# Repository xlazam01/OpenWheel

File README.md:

# OpenWheel

<p align="center"></p>

Open-source motorised filter wheel for astrophotography (up to 9 filters; the DIY release takes
4 × 2"). It appears on the PC as a USB serial device, is detected automatically, and is driven from
NINA and other ASCOM clients, or from KStars/Ekos through INDI.

## Documentation

| | |
|---|---|
| [Build guide](docs/BUILD.md) | step-by-step pages drawn from the CAD model, also as [PDF](docs/build/OpenWheel-build-guide.pdf) |
| [Bill of materials](docs/BOM.md) | printed, CNC and bought parts with sources; PCB parts with LCSC numbers ([CSV](docs/bom/)) |
| [User manual](docs/MANUAL.md) | mounting, drivers, buttons and LEDs, errors, changing filters, firmware update |
| [DIY notes](docs/DIY_NOTES.md) | every dimension and design decision behind the mechanics |
| [Schematic](docs/hw/OpenWheel-schematic.pdf) | PCB schematic (PDF); board renders: [top](docs/hw/pcb_top.png), [bottom](docs/hw/pcb_bottom.png), [3D](docs/hw/pcb_iso.png) |
| [Protocol](docs/PROTOCOL.md) | serial commands for your own software |

| | |
|---|---|
| MCU | STM32G0B1 (native USB CDC), PlatformIO + Arduino framework |
| Motor | stepper on a TMC2209 (UART configured) |
| Position | hall sensor + a different-length magnet per slot; calibration, filter names and focus offsets are stored in a 24AA64 I2C EEPROM |
| Host protocol | text commands `:NN[params]#`, 115200 baud, every command is answered |
| USB ID | VID `0x1209` ([pid.codes](https://pid.codes)), PID see [docs/USB_IDS.md](docs/USB_IDS.md) |

<p align="center">

</p>
<p align="center"><sub>Controller PCB (V3.2, rendered from <code>hw/filter_wheel.kicad_pcb</code>)</sub></p>

## Repository layout

| Folder | Content |
|---|---|
| `fw/` | firmware (PlatformIO project, target `STM32G0B1`) |
| `hw/` | KiCad schematic and PCB |
| `cad/diy/` | mechanical models of the DIY release (SolidCraft sources, STEP, 3MF for printing) |
| `driver/ASCOM/` | ASCOM driver for NINA & co.: core library, COM local server, setup dialog, tests, installer script |
| `driver/INDI/` | INDI driver for KStars/Ekos on Linux, wheel simulator, tests |
| `tools/gui/` | small Python/Qt test GUI |
| `tools/hwtest/` | pytest acceptance tests that run against a real board over USB |
| `tools/manual/` | generator for the build-guide pages (CAD view DXF → SVG/PDF) |
| `docs/` | build guide, BOM, user manual, DIY notes, protocol reference, USB IDs |
| `release/` | one folder per release: firmware binary, PCB fabrication files, CAD exports — latest [1.1.0](release/1.1.0/README.md) |

## Build and flash

```text
pio run -d fw -e STM32G0B1                 # build
pio run -d fw -e STM32G0B1 -t upload       # flash over USB (DFU)
```

**Entering the bootloader (DFU):**

- **Hold the CCW button while powering on.** The CCW button is wired to the **BOOT0** pin, so the
  STM32 starts its built-in USB DFU bootloader instead of the firmware.
- On a running wheel the command `:31#` does the same without touching the button (flag in RAM + reset, see
  [docs/BOOTLOADER.md](docs/BOOTLOADER.md)).

Open `fw/` (not the repository root) in VS Code with the PlatformIO extension.

## Using the wheel

- **Buttons:** single click on CW / CCW moves to the next / previous slot, double click homes,
  a long press on CW starts calibration. Holding **CW** while powering on also starts calibration;
  holding **CCW** while powering on enters DFU (see above).
- **LEDs:** status LED 1 blinks while moving; LED 2 blinks the slot number on arrival; both LEDs
  alternate on an error (read the cause with `:33#` / `:34#`).
- **Test GUI:** `pip install -r tools/gui/requirements.txt && python tools/gui/main.py`
- **Hardware tests:** `python -m pytest tools/hwtest --port COM13`

## Serial protocol

Full reference with every command: [docs/PROTOCOL.md](docs/PROTOCOL.md). In short:

- **Link:** USB CDC serial port (115200 8N1, the speed is nominal over USB). Do not rely on DTR.
- **Framing:** a command is `:NN[params]#` where `NN` is a two-digit command number. Bytes outside
  `:...#` are ignored; a new `:` restarts the command. Keep a command to 46 characters and send one
  at a time (a large burst can overrun the USB receive buffer and lose the `#`).
- **Every command is answered** with one line ending in `#`:

  | Answer | Meaning |
  |---|---|
  | `<value>#` | query result (number, text, or comma separated list) |
  | `OK#` | set / action accepted (a move answers as soon as it has started) |
  | `ERR,<code>#` | rejected, see error codes below |

- **Slots are numbered from 0.** Parameters accept `:07 3#`, `:07,3#` and `:073#`.
- **Identify first.** After power-on and each time a host opens the port, only `:25#` and `:32#`
  are accepted; anything else answers `ERR,16` until `:32#` has been sent (protocol 3, firmware 1.4).

Example session:

```text
:25#        ->  OK#                                       ping
:33#        ->  ERR,16#                                   not identified yet
:32#        ->  OPENWHEEL,G0B1,FW1.4.0,3,207834924B31#    identify: model, firmware, protocol version, serial
:33#        ->  S,1,0,-1,4,0,3#                           status: idle, slot 0, 4 slots, no error
:07 2#      ->  OK#                                       start moving to slot 2
:33#        ->  S,2,-1,2,4,0,3#                           moving (slot -1), target 2
:07 9#      ->  ERR,7#                                    bad parameter
:33#        ->  S,1,2,-1,4,0,3#                           arrived at slot 2
```

Main commands:

| Command | Purpose | Answer |
|---|---|---|
| `:25#` | ping | `OK#` |
| `:32#` | identify (automatic detection; unlocks all other commands) | `OPENWHEEL,model,firmware,protocol,serial#` |
| `:33#` | status | `S,state,slot,target,slots,error,flags#` |
| `:06#` | current slot, `-1` while moving or unknown | number |
| `:07 N#` | move to slot N | `OK#` |
| `:20#` | home | `OK#` |
| `:30#` | halt | `OK#` |
| `:35#` | start calibration | `OK#` |
| `:16#` | number of slots found by calibration | number |
| `:34#` / `:34,0#` | read / clear the sticky device error | `E,code#` / `OK#` |
| `:36#` / `:37 N,name#` | get all filter names / set the name of slot N | `a,b,c#` / `OK#` |
| `:38#` / `:39 N,offset#` | get all focus offsets / set the offset of slot N | `a,b,c#` / `OK#` |
| `:40#` | health: MCU temperature, supplies, driver temperature, warnings | `H,...#` (see docs/PROTOCOL.md) |
| `:41#` / `:42 N#` | stall detection: threshold and load readings / set threshold (0 = off) | `G,...#` / `OK#` |
| `:43#` / `:44 N#` | status LED brightness 0..100 % (0 = off) / set it | number / `OK#` |
| `:45#` | live Hall sensor state, also uncalibrated (magnet polarity check) | `1#` switched / `0#` |
| `:18#` / `:19#` | firmware version / name | text |
| `:31#` | reboot into the DFU bootloader | `OK#` |

**Status fields:** `state` 0 init, 1 idle, 2 moving, 3 homing, 4 calibrating, 5 error; `slot` is
the current slot (`-1` while moving or when the position is unknown); `target` the slot of a move;
`slots` the calibrated slot count (0 = not calibrated); `error` the sticky error code; `flags`
bit 0 calibrated, bit 1 position known, bit 2 button held at boot, bit 3 EEPROM fault, bit 4 health
warning (details with `:40#`).

**Error codes:**

| Code | Meaning | Code | Meaning |
|---|---|---|---|
| 0 | none | 7 | bad parameter |
| 1 | homing timed out | 8 | busy (moving, homing or calibrating) |
| 2 | move timed out | 9 | not calibrated |
| 3 | calibration failed | 10 | unknown command |
| 4 | EEPROM missing or write failed | 11 | malformed command |
| 5 | motor driver (TMC2209) fault | 12 | not changeable at runtime |
| 6 | no hall sensor pulse seen | 13 | motor stalled (stall detection) |

Codes 1 to 6 and 13 are device faults: the wheel signals them on the LEDs for 10 s and keeps the code
until it is cleared with `:34,0#`. Codes 7 to 12 are only returned in the reply to a rejected command.

**Filter names and focus offsets** (`:36` to `:39`) are stored in the wheel's EEPROM, in their own
region, so they survive a calibration reset and follow the wheel to any PC. A name has up to 15
printable ASCII characters and must not contain `,` `#` `:` or `|`.

## ASCOM driver (NINA and other clients)

`driver/ASCOM` contains an ASCOM Platform 7 driver (`IFilterWheelV3`, ProgID
`ASCOM.OpenWheel.FilterWheel`). It finds the wheel by its USB ID (VID `0x1209`) and then confirms it
with `:32#`, so there is no COM port to choose.

- `Position` is `-1` while the wheel moves; faults are reported as ASCOM exceptions with a readable reason.
- `Names` and `FocusOffsets` come from the wheel. The imaging software keeps its own filter list and
  can import these (NINA: clear its cached filter list after renaming).
- Extra actions: `Status` (JSON, including temperatures, supply voltages and warnings),
  `Home`, `Halt`, `ClearError`, `Calibrate` (parameter `confirm`).
- The setup dialog (gear icon in NINA) edits names and offsets, shows the live status and health
  (temperatures, supply, warnings) and offers Home, Halt, Clear error and Calibrate. Stall detection
  is set up there too: *Test move* measures the motor load and suggests a threshold, *Set* stores it
  in the wheel (0 = off). The status LED brightness (0 = off, for dark sites) is set there as well.
  *Magnet polarity* shows the live Hall sensor while a builder holds each loose magnet to it before
  gluing: SWITCHED = south pole at the sensor, that face goes outward (firmware 1.3+, no calibration needed).
- Health warnings (low supply, driver overtemperature or reset, crystal not running) are written to
  the log as they appear.
- It is built so that a silent, garbage-sending or unplugged device never hangs the client: every call
  is bounded in time, a lost connection is retried in the background, and a move that never ends is halted.
- Log file: `%LOCALAPPDATA%\OpenWheel\driver.log`.

Build and register for development (the second command asks for administrator rights itself):

```text
dotnet build driver/ASCOM/OpenWheel.Ascom -c Release
OpenWheel.Ascom.Server.exe /regserver          # use /unregserver to remove it
```

Tests: `dotnet test driver/ASCOM/OpenWheel.Core.Tests` (simulated misbehaving devices) and
`conformu conformance ASCOM.OpenWheel.FilterWheel` ([ConformU](https://github.com/ASCOMInitiative/ConformU)).

## INDI driver (KStars/Ekos on Linux)

`driver/INDI` contains `indi_openwheel`, an `INDI::FilterWheel` driver for libindi 2.x (Raspberry Pi,
Astroberry, StellarMate). It behaves like the ASCOM driver:

- It finds the wheel by its USB ID and confirms it with `:32#`.
- Filter names and focus offsets are stored in the wheel.
- It shows the status and health of the wheel, and offers Home, Halt, Calibrate and Clear error.
- Every command is bounded in time.

It comes with a simulated wheel (`openwheel_sim`) and tests against it. Building, installing and the
udev rule are described in [driver/INDI/README.md](driver/INDI/README.md). It has not been tested with
the real wheel yet.

## Status

The firmware (protocol v2) passes the hardware acceptance tests on a real board. The ASCOM driver
passes ConformU 4.5.2 with no errors, warnings or issues (report in `driver/ASCOM/conformance/`).
An Inno Setup installer script exists (`driver/ASCOM/installer/`) but has not been run yet; NINA field
testing is in progress.

## Acknowledgements

Many thanks to the authors of the [myFilterWheel ASCOM DIY](https://sourceforge.net/projects/myfilterwheel-ascom-diy/)
project (Robert Brown, Clive Stachon and contributors, MIT licence). The basic `:NN#` serial
protocol of OpenWheel was inspired by theirs and then extended with new features: acknowledged
replies, error codes, a status command and device identification for automatic detection.
OpenWheel is an independent project and is not affiliated with myFilterWheel.

## Support

OpenWheel is free and open source. If it saved you a weekend, tips go into the next build:
[ko-fi.com/curlycz](https://ko-fi.com/curlycz)

Want an assembled controller board or a complete wheel? Tell me at astro@martinlaza.eu. If enough
people ask, I'll make a small batch.

<!-- After the PCBWay shared-project upload, fill in the URL and uncomment:
You can also order the bare PCB from [PCBWay](https://www.pcbway.com/project/shareproject/XXXX); I get 10 % of the order.
-->

## Licences

- Software and firmware: GPL-3.0-or-later, see [LICENSE](LICENSE).
- Hardware design files (`hw/`, `cad/`): CERN-OHL-S-2.0, see [LICENSE-HARDWARE](LICENSE-HARDWARE).
- Vendored libraries in `fw/lib/` keep their own licences (TMCStepper, SparkFun External EEPROM).

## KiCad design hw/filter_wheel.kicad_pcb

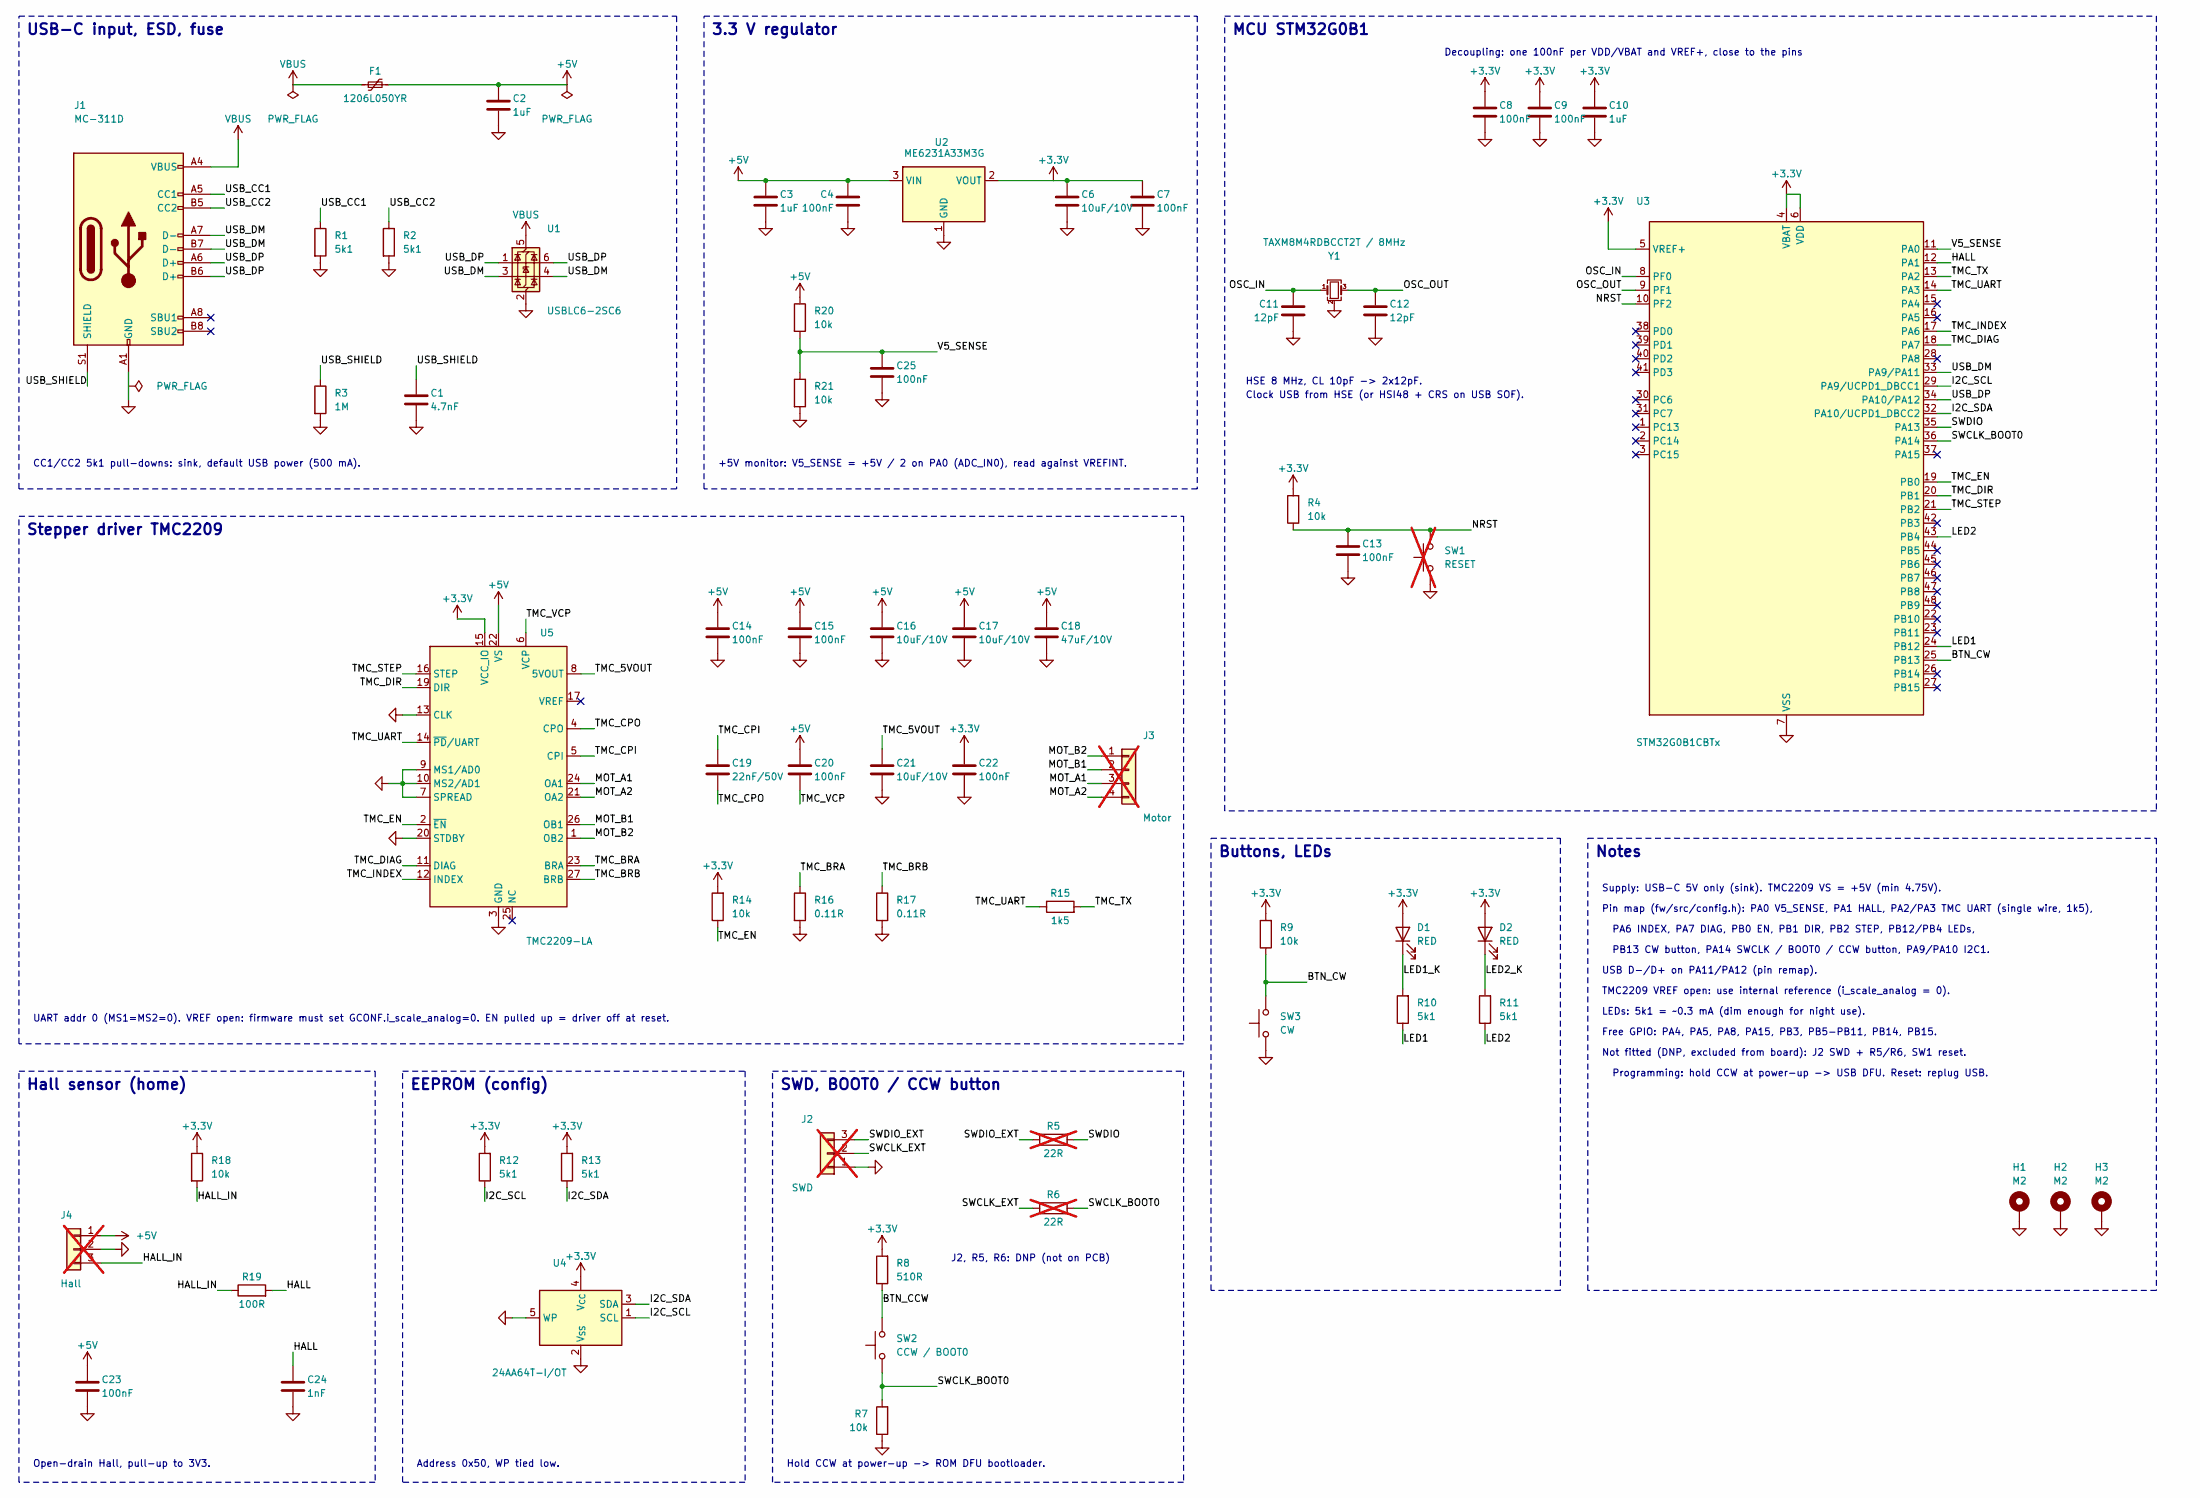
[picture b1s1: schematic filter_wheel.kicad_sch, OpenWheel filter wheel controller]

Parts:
C1: 4.7nF; C_0402_1005Metric; LCSC C1538
C2, C3, C10: 1uF; C_0402_1005Metric; LCSC C52923
C4, C7, C8, C9, C13, C14, C15, C20, C22, C23, C25: 100nF; C_0402_1005Metric; LCSC C1525
C6, C16, C17, C21: 10uF/10V; C_0402_1005Metric; LCSC C315248
C11, C12: 12pF; C_0402_1005Metric; LCSC C1547
C18: 47uF/10V; C_1206_3216Metric; LCSC C96123
C19: 22nF/50V; C_0402_1005Metric; LCSC C1532
C24: 1nF; C_0402_1005Metric; LCSC C1523
D1, D2: RED; LED_0603_1608Metric; LCSC C2286
F1: 1206L050YR; Fuse_1206_3216Metric; LCSC C163512
H1, H2, H3: M2; MountingHole_2.2mm_M2_DIN965_Pad
J1: MC-311D; USB_C_Receptacle_G-Switch_GT-USB-7010ASV; LCSC C2988369
J2: SWD; JST_PH_B3B-PH-K_1x03_P2.00mm_Vertical; not fitted
J3: Motor; JST_PH_B4B-PH-K_1x04_P2.00mm_Vertical; MPN JST B4B-PH-K; not fitted
J4: Hall; JST_PH_B3B-PH-K_1x03_P2.00mm_Vertical; MPN JST B3B-PH-K; not fitted
R1, R2, R10, R11, R12, R13: 5k1; R_0402_1005Metric; LCSC C25905
R3: 1M; R_0402_1005Metric; LCSC C26083
R4, R7, R9, R14, R18, R20, R21: 10k; R_0402_1005Metric; LCSC C25744
R5, R6: 22R; R_0402_1005Metric; not fitted
R8: 510R; R_0402_1005Metric; LCSC C25123
R15: 1k5; R_0402_1005Metric; LCSC C25867
R16, R17: 0.11R; R_0805_2012Metric; LCSC C5126077
R19: 100R; R_0402_1005Metric; LCSC C25076
SW1: RESET; SW_Push_SPST_NO_Alps_SKRK; MPN TS-1088-AR02016; not fitted
SW2: CCW / BOOT0; SW_Push_SPST_NO_Alps_SKRK; MPN TS-1088-AR02016; LCSC C720477
SW3: CW; SW_Push_SPST_NO_Alps_SKRK; MPN TS-1088-AR02016; LCSC C720477
U1: USBLC6-2SC6; SOT-23-6; LCSC C2687116
U2: ME6231A33M3G; SOT-23; LCSC C2765181
U3: STM32G0B1CBTx; LQFP-48_7x7mm_P0.5mm; LCSC C2847904
U4: 24AA64T-I/OT; SOT-23-5; LCSC C2061092
U5: TMC2209-LA; QFN-28-1EP_5x5mm_P0.5mm_EP3.75x3.75mm_ThermalVias; LCSC C2150710
Y1: TAXM8M4RDBCCT2T / 8MHz; Crystal_SMD_3225-4Pin_3.2x2.5mm; LCSC C400090

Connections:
+3.3V: C6.1, C7.1, C8.1, C9.1, C10.1, C22.2, D1.2 (A), D2.2 (A), R4.2, R8.2, R9.2, R12.2, R13.2, R14.2, R18.1, U2.2 (VOUT), U3.4 (VBAT), U3.5 (VREF+), U3.6 (VDD), U4.4 (V_{CC}), U5.15 (VCC_IO)
+5V: C2.2, C3.1, C4.1, C14.2, C15.2, C16.2, C17.2, C18.1, C20.1, C23.1, F1.2, J4.1, R20.1, U2.3 (VIN), U5.22 (VS), U5.28 (VS)
/BTN_CCW: R8.1, SW2.2
/BTN_CW: R9.1, SW3.2, U3.25 (PB13)
/HALL: C24.1, R19.2, U3.12 (PA1)
/HALL_IN: J4.3, R18.2, R19.1
/I2C_SCL: R12.1, U3.29 (PA9/UCPD1_DBCC1), U4.1 (SCL)
/I2C_SDA: R13.1, U3.32 (PA10/UCPD1_DBCC2), U4.3 (SDA)
/LED1: R10.1, U3.24 (PB12)
/LED1_K: D1.1 (K), R10.2
/LED2: R11.1, U3.43 (PB4)
/LED2_K: D2.1 (K), R11.2
/MOT_A1: J3.3, U5.24 (OA1)
/MOT_A2: J3.4, U5.21 (OA2)
/MOT_B1: J3.2, U5.26 (OB1)
/MOT_B2: J3.1, U5.1 (OB2)
/NRST: C13.1, R4.1, SW1.2, U3.10 (PF2)
/OSC_IN: C11.1, U3.8 (PF0), Y1.1
/OSC_OUT: C12.1, U3.9 (PF1), Y1.3
/SWCLK_BOOT0: R6.2, R7.2, SW2.1, U3.36 (PA14)
/SWDIO: R5.2, U3.35 (PA13)
/TMC_5VOUT: C21.2, U5.8 (5VOUT)
/TMC_BRA: R16.1, U5.23 (BRA)
/TMC_BRB: R17.1, U5.27 (BRB)
/TMC_CPI: C19.1, U5.5 (CPI)
/TMC_CPO: C19.2, U5.4 (CPO)
/TMC_DIAG: U3.18 (PA7), U5.11 (DIAG)
/TMC_DIR: U3.20 (PB1), U5.19 (DIR)
/TMC_EN: R14.1, U3.19 (PB0), U5.2 (~EN)
/TMC_INDEX: U3.17 (PA6), U5.12 (INDEX)
/TMC_STEP: U3.21 (PB2), U5.16 (STEP)
/TMC_TX: R15.2, U3.13 (PA2)
/TMC_UART: R15.1, U3.14 (PA3), U5.14 (~PD/UART)
/TMC_VCP: C20.2, U5.6 (VCP)
/USB_CC1: J1.A5 (CC1), R1.1
/USB_CC2: J1.B5 (CC2), R2.1
/USB_DM: J1.A7 (D-), J1.B7 (D-), U1.3 (I/O2), U1.4 (I/O2), U3.33 (PA9/PA11)
/USB_DP: J1.A6 (D+), J1.B6 (D+), U1.1 (I/O1), U1.6 (I/O1), U3.34 (PA10/PA12)
/USB_SHIELD: C1.1, J1.S1 (SHIELD), R3.1
/V5_SENSE: C25.1, R20.2, R21.1, U3.11 (PA0)
GND: C1.2, C2.1, C3.2, C4.2, C6.2, C7.2, C8.2, C9.2, C10.2, C11.2, C12.2, C13.2, C14.1, C15.1, C16.1, C17.1, C18.2, C21.1, C22.1, C23.2, C24.2, C25.2, H1.1 (1_1), H2.1 (1_1), H3.1 (1_1), J1.A1 (GND), J1.A12 (GND), J1.B1 (GND), J1.B12 (GND), J2.1, J4.2, R1.2, R2.2, R3.2, R7.1, R16.2, R17.2, R21.2, SW1.1, SW3.1, U1.2 (GND), U2.1 (GND), U3.7 (VSS), U4.2 (V_{SS}), U4.5 (WP), U5.3 (GND), U5.7 (SPREAD), U5.9 (MS1/AD0), U5.10 (MS2/AD1), U5.13 (CLK), U5.18 (GND), U5.20 (STDBY), U5.29 (GND), Y1.2 (G), Y1.4 (G)
unnamed: J2.2, R6.1
unnamed: J2.3, R5.1
VBUS: F1.1, J1.A4 (VBUS), J1.A9 (VBUS), J1.B4 (VBUS), J1.B9 (VBUS), U1.5 (VBUS)

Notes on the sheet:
Buttons, LEDs
Not fitted (DNP, excluded from board): J2 SWD + R5/R6, SW1 reset.
Hall sensor (home)
TMC2209 VREF open: use internal reference (i_scale_analog = 0).
Decoupling: one 100nF per VDD/VBAT and VREF+, close to the pins
CC1/CC2 5k1 pull-downs: sink, default USB power (500 mA).
Clock USB from HSE (or HSI48 + CRS on USB SOF).
MCU STM32G0B1
USB D-/D+ on PA11/PA12 (pin remap).
PA6 INDEX, PA7 DIAG, PB0 EN, PB1 DIR, PB2 STEP, PB12/PB4 LEDs,
Open-drain Hall, pull-up to 3V3.
EEPROM (config)
J2, R5, R6: DNP (not on PCB)
Stepper driver TMC2209
PB13 CW button, PA14 SWCLK / BOOT0 / CCW button, PA9/PA10 I2C1.
Pin map (fw/src/config.h): PA0 V5_SENSE, PA1 HALL, PA2/PA3 TMC UART (single wire, 1k5),
Supply: USB-C 5V only (sink). TMC2209 VS = +5V (min 4.75V).
Hold CCW at power-up -> ROM DFU bootloader.
UART addr 0 (MS1=MS2=0). VREF open: firmware must set GCONF.i_scale_analog=0. EN pulled up = driver off at reset.
3.3 V regulator
Notes
Programming: hold CCW at power-up -> USB DFU. Reset: replug USB.
+5V monitor: V5_SENSE = +5V / 2 on PA0 (ADC_IN0), read against VREFINT.
LEDs: 5k1 = ~0.3 mA (dim enough for night use).
USB-C input, ESD, fuse
Free GPIO: PA4, PA5, PA8, PA15, PB3, PB5-PB11, PB14, PB15.
HSE 8 MHz, CL 10pF -> 2x12pF.
Address 0x50, WP tied low.
SWD, BOOT0 / CCW button

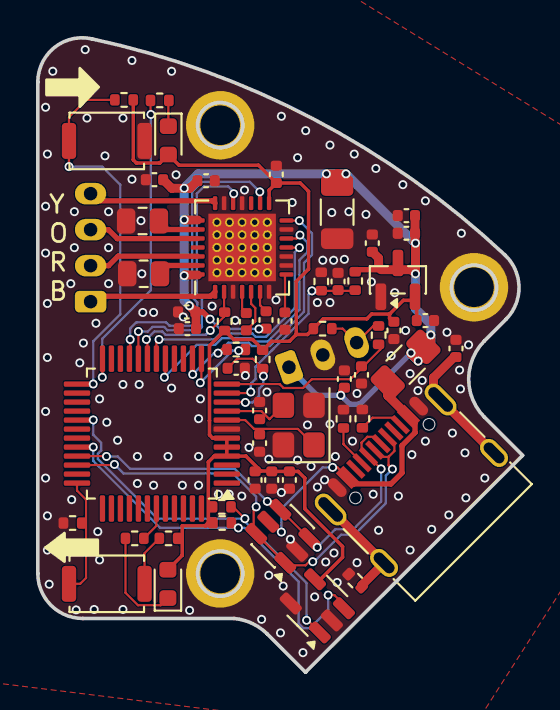
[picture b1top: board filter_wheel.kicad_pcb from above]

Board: 2 copper layers, 26.9 x 35.2 mm, 61 parts (1 on the bottom side), 41 nets.

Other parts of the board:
G1: Logo_WorksOnMySky_13mm

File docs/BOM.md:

# Bill of materials

Everything needed to build one OpenWheel (DIY release 1, 4 × 2" filters). Quantities are counted from
the CAD model (`cad/diy/ofw_diy_assembly`). Sources are examples, not requirements:

- **Mechanical parts:** AliExpress. Where a link is given, it is the listing the prototype parts were
  bought from (pick the variant with the dimensions in the table); listings change, so every line also
  has a search term.
- **Electronics:** LCSC part numbers, so the board can be assembled by JLCPCB. Same table as CSV:
  [bom/electronics.csv](bom/electronics.csv) (JLCPCB format), mechanical: [bom/mechanical.csv](bom/mechanical.csv).

Lines marked **?** are not decided yet or not tested on the prototype.

## 1. Printed parts

| # | Part | Qty | File | Notes |
|---|---|---|---|---|
| P1 | Shell | 1 | `cad/diy/ofw_diy_shell.3mf` | Opaque black (prototype: Prusament Galaxy Black). Scale X/Y to fit the plates, see the build guide |
| P2 | Wheel | 1 | `cad/diy/ofw_diy_wheel.3mf` | Opaque black |
| P3 | Motor box | 1 | `cad/diy/ofw_diy_motorbox.3mf` | Any colour (prototype: red), on its plate-side face, no supports |
| P4 | Motor box lid | 1 | `cad/diy/ofw_diy_motorbox_lid.3mf` | Same colour as the box, outer face down, no supports |

Print settings (layer height, walls, infill, material): **?** recorded after the test print (#5).

## 2. CNC plates

| # | Part | Qty | File | Notes |
|---|---|---|---|---|
| M1 | Front plate | 1 | `cad/diy/ofw_diy_plate_front.step` | JLCPCB CNC, aluminium 6061, 3 mm, matt black anodised. Threads: 1 × M48 × 0.75 (aperture), 6 × M2.5. Ask for "deburr all edges" |
| M2 | Camera plate | 1 | `cad/diy/ofw_diy_plate_camera.step` | Same. Threads: 6 × M2.5 |
| M2′ | Camera plate, M42 variant (instead of M2) | (1) | `cad/diy/ofw_diy_plate_camera_m42.step` | Same. Thread: 1 × M42 × 0.75 (aperture, Ø41.25 bore). For ZWO cooled cameras with the T2 ring removed (ASI183MC/MM Pro), see [DIY notes](DIY_NOTES.md#m42-camera-plate-variant) |

## 3. Bought mechanical parts

| # | Part | Qty | Specification | AliExpress | Notes |
|---|---|---|---|---|---|
| B1 | Standoff M3 × 15, round | 12 | Ø5, female–female, threaded ≥ 6.5 mm deep each end | [prototype listing](https://www.aliexpress.com/item/1005004063804402.html), `M3 round aluminium standoff female 15mm` | Aluminium, black. File all 12 to the same length |
| B2 | Screw M3 × 8, flat low head | 20 | Black, 12.9, hex 2, head Ø5.8 × 1.0 | `M3 ultra low head screw 12.9 black` | Plates to standoffs: 12 front, 8 camera |
| B3 | Screw M3 × 16, button head ISO 7380 | 4 | Hex 2 | `ISO7380 M3x16 button head` | Motor box to standoffs. Not shorter than 16 |
| B4 | Screw M3 × 8, button head ISO 7380 | 2 | Hex 2 | `ISO7380 M3x8 button head` | Motor ears. Not longer than 10 mm |
| B5 | Self-tapping screw M2 × 6, socket cap | 15 | For plastic, head Ø3.6 × 1.8, hex 1.5 | `M2x6 self tapping socket cap screw plastic` | 12 filter clamps + 3 PCB |
| B6 | O-ring 2 × 1 mm | 12 | NBR, ID 2, cross-section 1 | `O ring 2x1mm NBR` | One under each clamp screw head |
| B7 | Ball bearing MF105ZZ | 2 | 5 × 10 × 4, flange Ø11.2 × 0.8, shielded | `MF105ZZ flange bearing` | Flange on the chamber side |
| B8 | Shim washer 10 × 14 × 0.3 | 2 | DIN 988, stainless | [prototype listing](https://www.aliexpress.com/item/1005002301164770.html), `DIN988 shim 10x14x0.3` | Under each bearing flange |
| B9 | Shim washer 5 × 7 × 0.5 | 2 | DIN 988, stainless | [prototype listing](https://www.aliexpress.com/item/1005002301164770.html), `DIN988 shim 5x7x0.5` | On the shaft, between bearing and wheel |
| B10 | Shaft Ø5 × 20 mm | 1 | Stainless dowel pin, 304 | [prototype listing](https://www.aliexpress.com/item/4000473863693.html), `stainless dowel pin 5x20` | Press fit in the wheel |
| B11 | Magnet Ø6 × 3 mm | 10 | NdFeB N35 or stronger, axially magnetised | `neodymium magnet 6x3mm` | Buy a few spare |
| B12 | Stepper motor NEMA11 pancake | 1 | 28 × 28 × 9.5 mm, round, 1.8°, 0.5 A, 1 Ncm, bipolar 4 wires, **Ø3 mm shaft** | [STEPPERONLINE](https://www.aliexpress.com/item/4000182527052.html), `nema 11 pancake stepper 9.5mm` | Ears with M3 threads 34 mm apart |
| B13 | Silicone tube (friction drive) | 1 piece | ID 2 × OD 4 mm, stretched over the Ø3 shaft, cut flush with the shaft end | `silicone tube 2x4mm` | Pushed onto the motor shaft, runs on the wheel rim. No pulley, no belt |
| B14 | Hall sensor A3144 | 1 | Unipolar, TO-92UA | `A3144 hall sensor` | Soldered to the PCB, see the build guide |
| B15 | 2" filters, mounted | 4 | Ø50.8 × 5 mm cell, M48 × 0.75 thread ≤ 2 mm | — | Low-profile cells. Unmounted glass: **?** (#1) |
| B16 | Screws M2.5 for the camera | 6 + 6 | Length per camera / adapter | `M2.5 socket cap screw` | Camera side and telescope side |
| B17 | Thread-locking / retaining compound, super glue | — | e.g. Loctite 641 for loose bearings, CA glue for magnets | — | |

## 4. Electronics

The board (`hw/`) is assembled by JLCPCB from the files in `hw/`. J3 and J4 are not fitted: the motor
wires and the Hall sensor are soldered to their pads. "Basic" parts cost no feeder fee at JLCPCB.

| Ref | Value | Package | LCSC | Type |
|---|---|---|---|---|
| C1 | 4.7 nF | 0402 | C1538 | basic |
| C2, C3, C10 | 1 µF | 0402 | C52923 | basic |
| C4, C7, C8, C9, C13, C14, C15, C20, C22, C23, C25 | 100 nF | 0402 | C1525 | basic |
| C19 | 22 nF 50 V | 0402 | C1532 | basic |
| C6, C16, C17, C21 | 10 µF 10 V | 0402 | C315248 | extended (no 10 V basic part) |
| C11, C12 | 12 pF C0G | 0402 | C1547 | basic |
| C18 | 47 µF 10 V | 1206 | C96123 | basic |
| C24 | 1 nF | 0402 | C1523 | basic |
| D1, D2 | LED red | 0603 | C2286 | basic |
| F1 | Polyfuse 0.5 A, SMD0603P050TF | 0603 | C20789 | extended |
| J1 | USB-C receptacle GT-USB-7010ASV | SMD | C2988369 | extended |
| J3, J4 | JST PH 4-pin / 3-pin | — | — | **not fitted** |
| R1, R2, R10, R11, R12, R13 | 5.1 kΩ | 0402 | C25905 | basic |
| R3 | 1 MΩ | 0402 | C26083 | basic |
| R4, R7, R9, R14, R18, R20, R21 | 10 kΩ | 0402 | C25744 | basic |
| R8 | 510 Ω | 0402 | C25123 | basic |
| R15 | 1.5 kΩ | 0402 | C25867 | basic |
| R16, R17 | 0.11 Ω (motor current sense) | 0805 | C5126077 | extended |
| R19 | 100 Ω | 0402 | C25076 | basic |
| SW2, SW3 | Tactile switch TS-1088-AR02016 | SMD 4 × 3 | C720477 | basic |
| U1 | USBLC6-2SC6 (USB ESD) | SOT-23-6 | C2687116 | extended |
| U2 | ME6231A33M3G (3.3 V LDO, 500 mA; same part as AstroUniBoard U1) | SOT-23 | C2765181 | extended |
| U3 | STM32G0B1CBT6 | LQFP-48 | C2847904 | extended; was out of stock at JLCPCB on 2026-11-04. The chip is common elsewhere (LCSC, Mouser, AliExpress, e.g. the WeAct Studio store, which also sells an STM32G0B1 core board): buy it there and consign it to JLCPCB, or solder it yourself |
| U4 | 24AA64T-I/OT (EEPROM) | SOT-23-5 | C2061092 | extended |
| U5 | TMC2209-LA-T (stepper driver) | QFN-28 | C2150710 | extended |
| Y1 | 8 MHz crystal TAXM8M4RDBCCT2T | 3225 | C400090 | extended |

PCB: 2 layers, 1.6 mm. Board outline and fabrication settings: `hw/filter_wheel.kicad_pcb`.

## 5. Tools

- Hex keys 1.5, 2, 2.5 mm; small Phillips/flat screwdriver
- Micrometer or caliper (standoffs, hub height), flat file or sandpaper on a flat plate (P400–P800)
- Vice or arbor press (shaft into the wheel)
- Soldering iron (Hall sensor, motor wires), side cutters
- Multimeter (magnet polarity, see the build guide)
- USB-C cable, PC with the OpenWheel ASCOM driver

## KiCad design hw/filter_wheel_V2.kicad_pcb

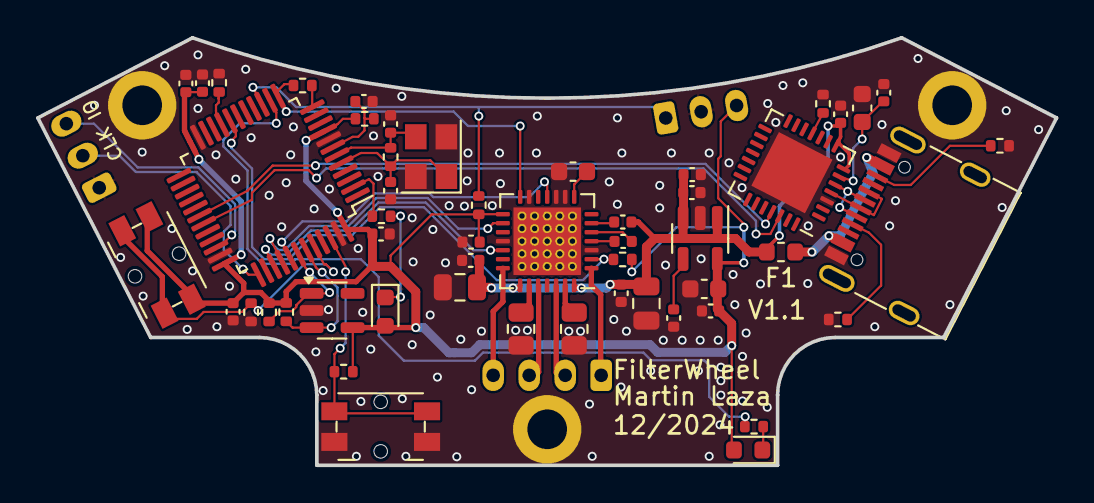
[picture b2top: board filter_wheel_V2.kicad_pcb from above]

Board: 2 copper layers, 56.6 x 23.8 mm, 58 parts (0 on the bottom side), 44 nets.

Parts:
C1, C6, C10, C11: 1uF; C_0402_1005Metric
C2, C24: 10uF/10V; C_0603_1608Metric
C3, C7, C8, C9, C12, C15: 100nF; C_0402_1005Metric
C4, C5: 20pF; C_0402_1005Metric
C13: 22nF; C_0402_1005Metric
C14: 10uF; C_0603_1608Metric
C16, C17: 4.7u/25V; C_0805_2012Metric
C18: 22n/50V; C_0402_1005Metric
C19, C20, C21, C22: 100n/50V; C_0402_1005Metric
D1, D2: LED; LED_0603_1608Metric
F1: SMD0603P050TF; Fuse_0603_1608Metric
H1, H2, H3: MountingHole_Pad; MountingHole_2.2mm_M2_DIN965_Pad
J1, J4: Conn_01x03; JST_PH_B3B-PH-K_1x03_P2.00mm_Vertical
J2: MC-311D; USB_C_Receptacle_G-Switch_GT-USB-7010ASV
J3: Conn_01x04; JST_PH_B4B-PH-K_1x04_P2.00mm_Vertical
R1, R3, R4, R5, R13, R15: 10k; R_0402_1005Metric
R2: 1MEG; R_0402_1005Metric
R6, R14: 510R; R_0402_1005Metric
R7, R8: 5k1; R_0402_1005Metric
R9: 100k; R_0402_1005Metric
R10, R11: 0.11R/0805; R_0805_2012Metric
R12: 1k; R_0402_1005Metric
R16, R17: 4k7; R_0402_1005Metric
RST2, RST3: EVQPUM; Panasonic_EVQPUM_EVQPUD
RT1: RT9193-3.3; SOT-23-5
U1: CP2102N-Axx-xQFN28; QFN-28-1EP_5x5mm_P0.5mm_EP3.35x3.35mm
U2: STM32F301C6Tx; LQFP-48_7x7mm_P0.5mm
U3: QFN-28-1EP_5x5mm_P0.5mm_EP3.75x3.75mm_ThermalVias
U4: 24AA02E-OT; SOT-23-5
Y1: TAXM8M4RDBCCT2T / 8MHz; Crystal_SMD_3225-4Pin_3.2x2.5mm

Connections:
+3.3V: C7.1, C8.1, C9.1, C10.1, C14.1, C15.1, C22.2, D1.2 (A), D2.2 (A), J4.3, R3.2, R9.2, R13.1, R15.2, R16.2, R17.2, RST2.2, RT1.5 (VOUT), U2.9 (VDDA), U2.24 (VDD), U2.36 (VDD), U2.48 (VDD), U3.15 (VCC_IO), U4.4 (V_{CC})
+5V: C1.2, C11.1, C12.1, C16.1, C17.1, C19.2, C20.2, C21.1, F1.2, RT1.1 (VIN), RT1.3 (EN), U1.7 (VREGIN), U1.8 (VBUS), U3.22 (VS), U3.28 (VS)
/BOOT0: R4.2, RST2.1, U2.44 (BOOT0)
/BOOT1: R5.1, U2.20 (PB2)
/DM1: J2.A7 (D-), J2.B7 (D-), U1.5 (D-)
/DP1: J2.A6 (D+), J2.B6 (D+), U1.4 (D+)
/NRST: C6.1, R3.1, U2.7 (NRST)
/OSCIN: C4.1, R2.1, U2.5 (PF0), Y1.1
/OSCOUT: C5.1, R2.2, U2.6 (PF1), Y1.3
/RX1: U1.26 (TXD), U2.31 (PA10)
/SWDCLK: J1.2, U2.37 (PA14)
/SWDIO: J1.3, U2.34 (PA13)
/TX1: U1.25 (RXD), U2.30 (PA9)
/TX2: R12.2, U2.12 (PA2)
DIAG: U2.41 (PB5), U3.11 (DIAG)
DIR: U2.39 (PB3), U3.19 (DIR)
EN: R9.1, U2.19 (PB1), U3.2 (ENN)
GND: C1.1, C2.2, C3.2, C4.2, C5.2, C6.2, C7.2, C8.2, C9.2, C10.2, C11.2, C12.2, C13.2, C14.2, C15.2, C16.2, C17.2, C19.1, C20.1, C22.1, C24.1, H1.1, H2.1, H3.1, J1.1, J2.A1 (GND), J2.A12 (GND), J2.B1 (GND), J2.B12 (GND), J4.2, R1.1, R4.1, R5.2, R7.2, R8.2, R10.2, R11.2, RST3.1, RT1.2 (GND), U1.3 (GND), U1.29 (GND), U2.8 (VSSA), U2.23 (VSS), U2.35 (VSS), U2.47 (VSS), U3.3 (GND), U3.9 (MS1_AD0), U3.10 (MS2_AD1), U3.13 (CLK), U3.18 (GND), U3.29 (GND), U4.2 (V_{SS}), Y1.2, Y1.4
unnamed: D1.1 (K), R6.2
unnamed: D2.1 (K), R14.2
unnamed: F1.1, J2.A4 (VBUS), J2.A9 (VBUS), J2.B4 (VBUS), J2.B9 (VBUS)
unnamed: J2.A5 (CC1), R7.1
unnamed: J2.B5 (CC2), R8.1
unnamed: J3.1, U3.1 (OUTB2)
unnamed: J3.2, U3.26 (OUTB1)
unnamed: J3.3, U3.24 (OUTA1)
unnamed: J3.4, U3.21 (OUTA2)
unnamed: J4.1, R13.2, U2.15 (PA5)
unnamed: C13.1, RT1.4 (BP)
unnamed: C2.1, C3.1, U1.6 (VDD)
unnamed: R1.2, U1.11 (~SUSPEND)
unnamed: R14.1, U2.14 (PA4)
unnamed: R15.1, RST3.2, U2.46 (PB9)
unnamed: R6.1, U2.2 (PC13)
unnamed: C24.2, U3.8 (5VOUT)
unnamed: R11.1, U3.23 (BRA)
unnamed: R10.1, U3.27 (BRB)
unnamed: C18.1, U3.5 (CPI)
unnamed: C18.2, U3.4 (CPO)
unnamed: C21.2, U3.6 (VCP)
SCL: R16.1, U2.42 (PB6), U4.1 (SCL)
SDA: R17.1, U2.43 (PB7), U4.3 (SDA)
STEP: U2.40 (PB4), U3.16 (STEP)
TMC_UART: R12.1, U2.13 (PA3), U3.14 (PDN_UART)

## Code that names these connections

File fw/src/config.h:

// STM32G0B1 Board Configuration
// Based on WeAct Studio STM32G0B1 development board schematic
#pragma once
#include <Arduino.h>

// Firmware information
#define FIRMWARE_NAME    "OpenWheel"
#define FIRMWARE_VERSION "FW1.4.0"

// Board revision (set by the PlatformIO environment)
//   1 = prototype board: no +5V sense divider, TMC2209 INDEX not connected
//   2 = redesigned board: +5V sense divider on PA0, TMC2209 INDEX on PA6
#ifndef HW_REV
#define HW_REV 1
#endif
#define HAS_V5_SENSE   (HW_REV >= 2)
#define HAS_TMC_INDEX  (HW_REV >= 2)

// USB CDC Serial Configuration
// STM32G0B1 has native USB support - use USB CDC for Serial communication
// This allows the device to appear as a virtual COM port when connected via USB
#define ENABLE_USB_CDC 1  // 1=enable USB CDC serial, 0=use UART

// Debug output control
#define DEBUG_ENABLED 0  // 1=enable debug messages, 0=disable

// Debug print macros
// On STM32G0B1 with USB CDC enabled, Serial goes over USB (SerialUSB)
#if DEBUG_ENABLED
  #if ENABLE_USB_CDC
    #define DEBUG_PRINT(...)    SerialUSB.print(__VA_ARGS__)
    #define DEBUG_PRINTLN(...)  SerialUSB.println(__VA_ARGS__)
    #define DEBUG_PRINTF(...)   SerialUSB.printf(__VA_ARGS__)
  #else
    #define DEBUG_PRINT(...)    Serial.print(__VA_ARGS__)
    #define DEBUG_PRINTLN(...)  Serial.println(__VA_ARGS__)
    #define DEBUG_PRINTF(...)   Serial.printf(__VA_ARGS__)
  #endif
#else
  #define DEBUG_PRINT(...)
  #define DEBUG_PRINTLN(...)
  #define DEBUG_PRINTF(...)
#endif

// Serial protocol: OpenWheel (":NN[params]#")
//   2 = every command is acknowledged
//   3 = identify first: only :25# and :32# until the host has identified the device (ERR,16)
#define PROTOCOL_VERSION 3
#define DEVICE_MODEL     "G0B1"

// Serial speed (UART builds; USB CDC ignores it)
#define SERIALPORTSPEED 115200

// Serial port abstraction for protocol communication
// This allows protocols to work with both USB CDC and hardware UART
#if ENABLE_USB_CDC
  #define PROTOCOL_SERIAL SerialUSB  // Use USB CDC for protocol commands
#else
  #define PROTOCOL_SERIAL Serial     // Use hardware UART
#endif

// External EEPROM (I2C) settings
#define EEPROMSIZE 8192 // 24AA64 (8Kbit = 8192 bytes)
#define EEPROM_ADDRESS 0b1010000 // 0x50 (A2=A1=A0=0)

// Startup behavior options
#define STARTUP_BEHAVIOR_STAY       0  // Stay at current position
#define STARTUP_BEHAVIOR_VERIFY     1  // Verify current position by detecting next magnet
#define STARTUP_BEHAVIOR_HOME       2  // Always go to home position

// Startup behavior configuration
#define STARTUP_BEHAVIOR STARTUP_BEHAVIOR_HOME  // Default: find home on startup

// Motor rotation direction
#define ROTATION_DIRECTION_CW   0  // Clockwise rotation
#define ROTATION_DIRECTION_CCW  1  // Counter-clockwise rotation
#define ROTATION_DIRECTION ROTATION_DIRECTION_CCW  // Default: counter-clockwise

// Hall sensor
#define HALLACTIVETYPE 2     // 1=active HIGH, 2=active LOW

// Limits
#define MAXSTEPS 100000L
#define MAX_SLOTS 9
#define BASE_OFFSET 308  // Base offset for wheel geometry (in steps)

// Motor current settings (mA)
// HW_REV 1 keeps the TMC2209 default i_scale_analog = 1: VREF is unconnected, so the real current
// is this value scaled by whatever VREF floats to. That setup is proven on the prototype. A true
// 400 mA (i_scale_analog = 0) browned out the driver: the whole board runs from USB 5V behind a
// 0.5 A polyfuse. HW_REV 2 uses the internal reference with a lower, still to be verified current.
#if HW_REV >= 2
#define DEFAULT_RUN_CURRENT_MA 250
#else
#define DEFAULT_RUN_CURRENT_MA 400
#endif
#define DEFAULT_HOLD_CURRENT_MA 100

// TMC2209 Driver Configuration
#define TMC_MICROSTEPS 0           // Microstepping mode (0, 2, 4, 8, 16, 32, 64, 128, 256)
#define TMC_TOFF 5                 // Off time setting (1-15). Higher = smoother but noisier. 0=driver disabled
#define TMC_HOLD_MULTIPLIER 0.5    // Hold current multiplier (0.0-1.0). Reduces current when motor is idle
#define TMC_PWM_AUTOSCALE 1        // Enable automatic PWM amplitude scaling (0=disabled, 1=enabled)

// StallGuard4 (stall -> DIAG). Threshold SGTHRS is stored in the EEPROM (:42), 0 = detection off.
// A stall is flagged when SG_RESULT <= 2 * SGTHRS while the motor runs faster than STALL_MIN_SPEED.
#define STALL_MIN_SPEED   500      // steps/s; below this the driver ignores StallGuard (TCOOLTHRS)
#define STALL_BLANK_MS    200      // ignore DIAG this long after the motor starts (StealthChop settles)
#define SG_SAMPLE_MS      20       // SG_RESULT sampling period during :21 step moves (tuning data)

// Housekeeping (MCU temperature, +5V rail)
#define V5_DIVIDER        2        // +5V sense divider ratio (10k / 10k)
#define V5_LOW_MV         4750     // warning below this (TMC2209 VS minimum)
#define HK_IDLE_MS        1000     // full housekeeping sample period
#define HK_MOVE_MS        5        // +5V sample period while the motor runs
// ---------------------------------------------------------------------------
// Pin mapping (STM32G0B1 - WeAct Studio board compatible)
// Update these if you change wiring
// ---------------------------------------------------------------------------

// TMC2209 UART (USART2)
#define SW_RX            PA3  // USART2 RX (TMC2209 UART)
#define SW_TX            PA2  // USART2 TX (TMC2209 UART)
#define SERIAL_PORT      Serial2  // HardwareSerial port for TMC2209
#define DRIVER_ADDRESS   0b00  // TMC2209 Driver address according to MS1 and MS2

// TMC2209 Control Pins
#define EN_PIN           PB0  // Enable (active LOW)
#define DIR_PIN          PB1  // Direction
#define STEP_PIN         PB2  // Step
#define DIAG_PIN         PA7  // Diagnostic output from TMC2209 (driver error or stall)
#define INDEX_PIN        PA6  // TMC2209 INDEX, configured as overtemperature prewarning (HW_REV 2)

// +5V rail sense (HW_REV 2): +5V / V5_DIVIDER on ADC_IN0
#define PIN_V5_SENSE     PA0

// Unused TMC pins (SPI mode - not used in UART mode)
#define CS_PIN           NULL  // Chip select
#define SW_MOSI          NULL  // Software Master Out Slave In (MOSI)
#define SW_MISO          NULL  // Software Master In Slave Out (MISO)
#define SW_SCK           NULL  // Software Slave Clock (SCK)

#define R_SENSE          0.11f // Match to your driver
                               // SilentStepStick series use 0.11
                               // UltiMachine Einsy and Archim2 boards use 0.2
                               // Panucatt BSD2660 uses 0.1
                               // Watterott TMC5160 uses 0.075

// Stepper motor performance settings
#define STEPPER_MAX_SPEED       1000   // Maximum motor speed (steps/sec)
#define STEPPER_SPEED           1000   // Current speed (steps/sec)
#define STEPPER_ACCEL           2000   // Stepper acceleration (steps/sec²)

// I2C (for external EEPROM)
// Note: STM32G0B1 uses I2C1 with AF6 on PA9/PA10
#define PIN_I2C_SCL      PA9   // I2C1 SCL (AF6)
#define PIN_I2C_SDA      PA10  // I2C1 SDA (AF6)

// USB (Native USB on STM32G0B1)
// Note: PA11/PA12 are dedicated USB pins on WeAct board
#define PIN_USB_DM       PA11  // USB D- (PA11)
#define PIN_USB_DP       PA12  // USB D+ (PA12)

// Hall sensor
#define PIN_HALL         PA1   // Hall effect sensor input

// Status LEDs (active LOW)
#define PIN_STATUS_LED1  PB12  // Status LED 1 (active LOW)
#define PIN_STATUS_LED2  PB4   // Status LED 2 (active LOW)

// User buttons
#define PIN_BUTTON       PB13  // Button for CW turn
#define PIN_BUTTON_CCW   PA14  // Button for CCW turn (shared with SWCLK/BOOT0)
                               // WARNING: PA14 is SWCLK - using it as button may interfere with debugging
                               // Consider external pull-up and careful schematic design

// Timer selection for stepper control
// STM32G0B1 has TIM1, TIM2, TIM3, TIM6, TIM7, TIM14, TIM15, TIM16, TIM17
// STM32G0B1 has no TIM4 - TIM3 is used
#define STEPPER_TIMER    TIM3  // Timer for stepper motor control 

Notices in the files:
hw/filter_wheel.kicad_sch:
Licence: CERN-OHL-S-2.0
